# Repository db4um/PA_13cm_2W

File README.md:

# PA 13cm 2W
Small 2W CW PA for the 13cm hamband. Great as a preamp for Eshail2. Size: 25mm x 25mm<br>
When this PA is used for SSB, a maximum output power of 1W (30dBm) is recommended to ensure linearity.<br>
Maximum measured output power was 34dBm (2.5W), but 36 dBm should be possible as well. 

The layout is built and impedance matched for the OSHpark 4-Layer process.
You can order the PCB directly from OSHpark: https://oshpark.com/projects/crZvjwqi

**Make sure to mount the PCB on a suitable heatsink**, as the PA dissipates up to 5W. (M2.5 screws)
Using thermal paste is recommended.

## Measured S-Parameter:

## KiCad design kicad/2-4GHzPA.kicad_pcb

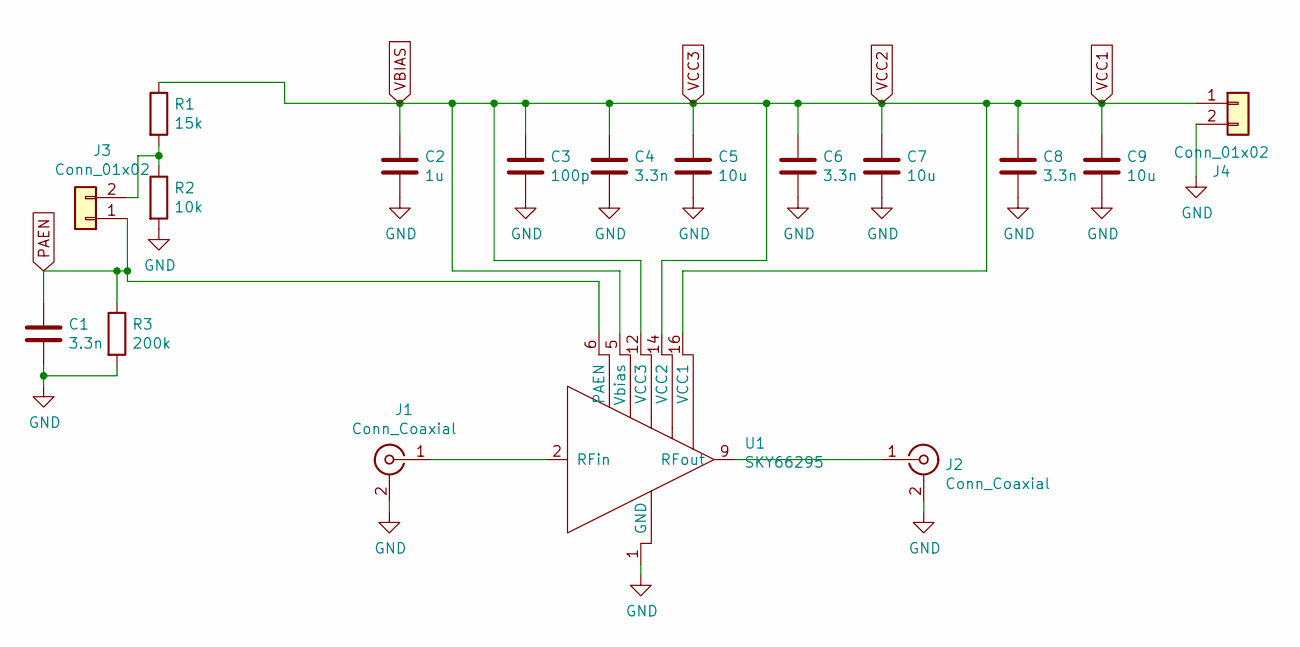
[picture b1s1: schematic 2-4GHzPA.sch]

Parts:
C1, C4, C6, C8: 3.3n; C_0603_1608Metric_Pad1.05x0.95mm_HandSolder
C2: 1u; C_0603_1608Metric_Pad1.05x0.95mm_HandSolder
C3: 100p; C_0603_1608Metric_Pad1.05x0.95mm_HandSolder
C5, C7, C9: 10u; C_1206_3216Metric_Pad1.42x1.75mm_HandSolder
J1, J2: Conn_Coaxial; SMA_Samtec_SMA-J-P-H-ST-EM1_EdgeMount
J3, J4: Conn_01x02; PinHeader_1x02_P2.54mm_Vertical
R1: 15k; R_0603_1608Metric_Pad1.05x0.95mm_HandSolder
R2: 10k; R_0603_1608Metric_Pad1.05x0.95mm_HandSolder
R3: 200k; R_0603_1608Metric_Pad1.05x0.95mm_HandSolder
U1: SKY66295; QFN-16_EP_5.3x5.3_Pitch0.8mm

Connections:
GND: C1.2, C2.2, C3.2, C4.2, C5.2, C6.2, C7.2, C8.2, C9.2, J1.2 (Ext), J2.2 (Ext), J4.2, R2.2, R3.2, U1.1 (GND), U1.3 (GND), U1.4 (GND), U1.7 (GND), U1.8 (GND), U1.10 (GND), U1.11 (GND), U1.13 (GND), U1.15 (GND), U1.17 (GND)
unnamed: J1.1 (In), U1.2 (RFin)
unnamed: J2.1 (In), U1.9 (RFout)
unnamed: J3.2, R1.2, R2.1
PAEN: C1.1, J3.1, R3.1, U1.6 (PAEN)
VBIAS: C2.1, C3.1, C4.1, C5.1, C6.1, C7.1, C8.1, C9.1, J4.1, R1.1, U1.5 (Vbias), U1.12 (VCC3), U1.14 (VCC2), U1.16 (VCC1)

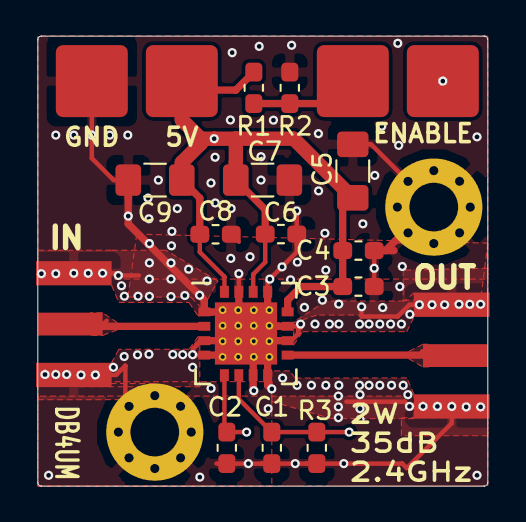
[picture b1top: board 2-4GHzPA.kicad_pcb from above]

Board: 4 copper layers, 25.0 x 25.0 mm, 17 parts (0 on the bottom side), 6 nets.

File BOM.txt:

BOM
2.4 GHz PA - DB4UM
Component Count:15
Ref		Qnty	Value	Part	Datasheet	Description	Vendor
C1, C4, C6, C8	4	3.3n	Device:C Size:0402		~	Unpolarized capacitor	
C2		1	1u	Device:C Size:0402		~	Unpolarized capacitor	
C3		1	100p	Device:C Size:0402		~	Unpolarized capacitor	
C5, C7, C9	3	10u	Device:C Size:1206		~	Unpolarized capacitor	
J1, J2		2	Conn_Coaxial	Connector:Conn_Coaxial	~	coaxial connector SMA	
R1		1	15k	Device:R Size:0402		~	Resistor	
R2		1	10k	Device:R Size:0402		~	Resistor	
R3		1	200k	Device:R			~	DO NOT INSERT	
U1		1	SKY66292-11

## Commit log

2019-03-06 first real commit
    added project files
2019-03-06 Update README.md
    pictures included
2019-03-06 Update README.md
    more markdown
2019-03-06 Update README.md
    ssb details
2019-03-06 Create BOM.txt.txt
    bom also included as a txt
2019-03-06 small bom fix
    corrected ic
2019-03-06 bom ic fixed
2019-03-14 missing kicad files
2019-04-27 added case
